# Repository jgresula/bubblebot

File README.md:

# BubbleBot

This repository contains firmware, FreeCAD and KiCad files for my [bubble blowing robot](http://make.bitovod.com/pages/bubblebot.html).

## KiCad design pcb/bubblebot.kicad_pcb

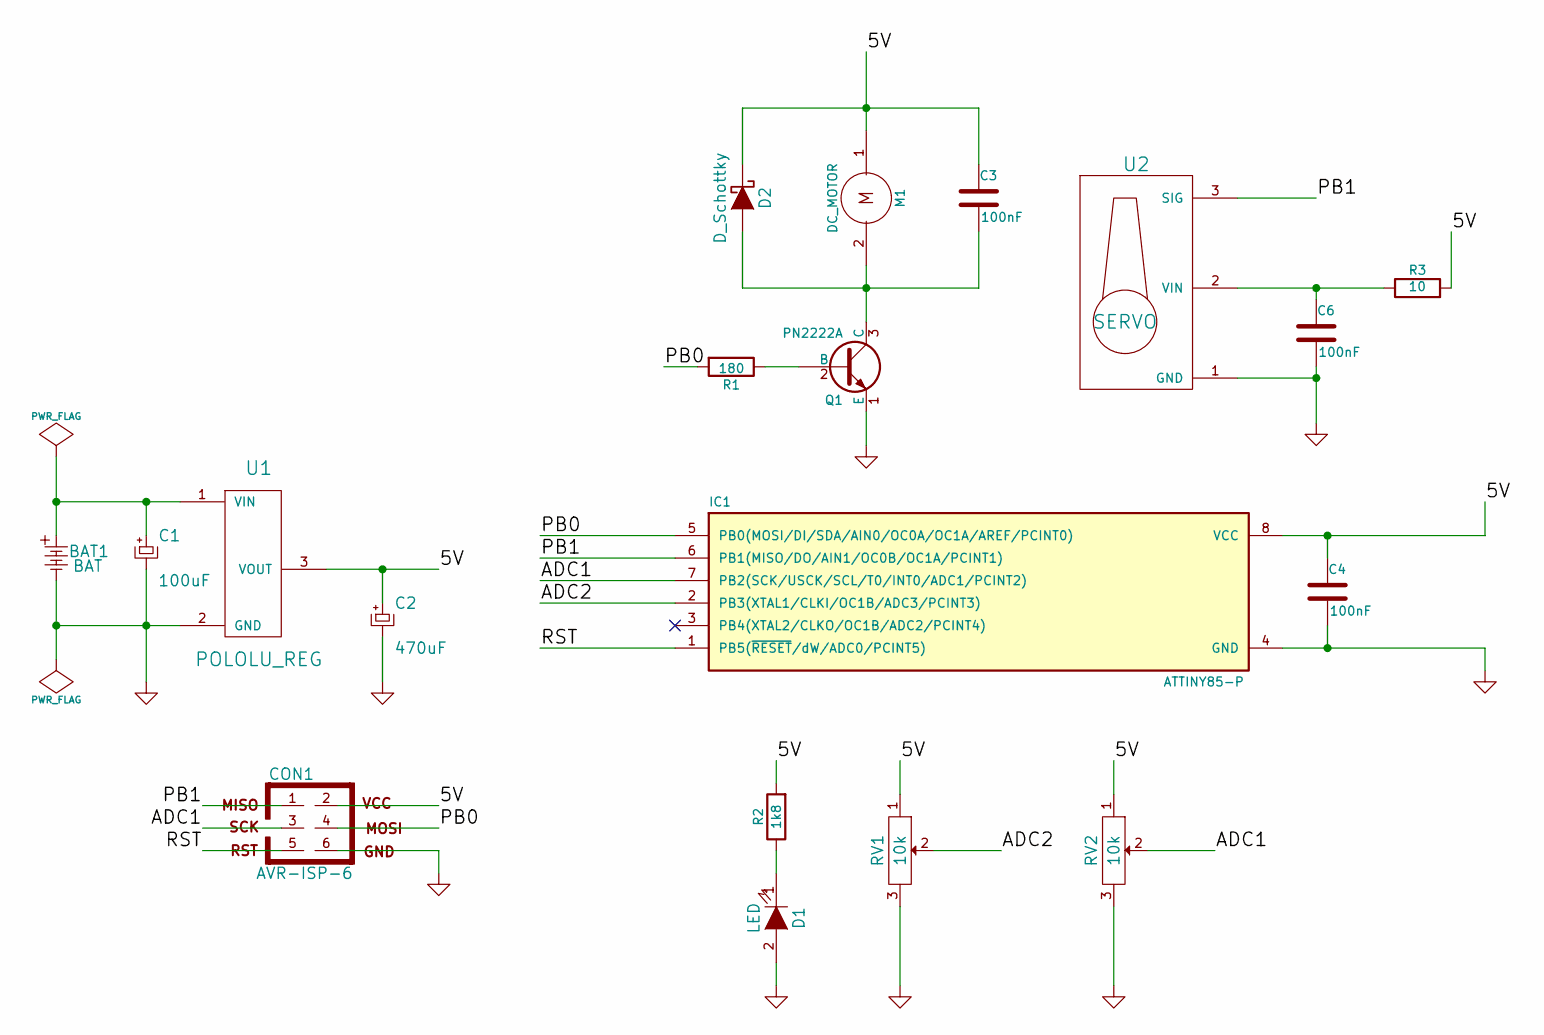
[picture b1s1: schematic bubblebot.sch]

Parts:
BAT1: BAT; Socket_Strip_Straight_1x02
C1: 100uF; C_Radial_D5_L11_P2
C2: 470uF; C_Radial_D8_L13_P3.8
C3, C4, C6: 100nF; C_Disc_D3_P2.5
CON1: AVR-ISP-6; Pin_Header_Straight_2x03
D1: LED; LED-3MM
D2: D_Schottky; Diode_DO-41_SOD81_Horizontal_RM10
IC1: ATTINY85-P; DIP-8_W7.62mm
M1: DC_MOTOR; Socket_Strip_Straight_1x02
Q1: PN2222A; TO-92_Molded_Narrow
R1: 180; Resistor_Vertical_RM5mm
R2: 1k8; Resistor_Vertical_RM5mm
R3: 10; Resistor_Vertical_RM5mm
RV1, RV2: 10k; Socket_Strip_Straight_1x03
U1: POLOLU_REG; Socket_Strip_Straight_1x03
U2: SERVO; Socket_Strip_Straight_1x03

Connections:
/5V: C2.1, C3.1, C4.1, CON1.2, D2.1 (K), IC1.8 (VCC), M1.1, R2.2, R3.2, RV1.1, RV2.1, U1.3 (VOUT)
/ADC1: CON1.3, IC1.7 (PB2(SCK/USCK/SCL/T0/INT0/ADC1/PCINT2)), RV2.2
/ADC2: IC1.2 (PB3(XTAL1/CLKI/OC1B/ADC3/PCINT3)), RV1.2
/PB0: CON1.4, IC1.5 (PB0(MOSI/DI/SDA/AIN0/OC0A/OC1A/AREF/PCI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), R1.2
/PB1: CON1.1, IC1.6 (PB1(MISO/DO/AIN1/OC0B/OC1A/PCINT1)), U2.3 (SIG)
/RST: CON1.5, IC1.1 (PB5(~RESET~/dW/ADC0/PCINT5))
GND: BAT1.2, C1.2, C2.2, C4.2, C6.2, CON1.6, D1.2 (A), IC1.4 (GND), Q1.1 (E), RV1.3, RV2.3, U1.2 (GND), U2.1 (GND)
unnamed: BAT1.1, C1.1, U1.1 (VIN)
unnamed: C3.2, D2.2 (A), M1.2, Q1.3 (C)
unnamed: C6.1, R3.1, U2.2 (VIN)
unnamed: D1.1 (K), R2.1
unnamed: Q1.2 (B), R1.1

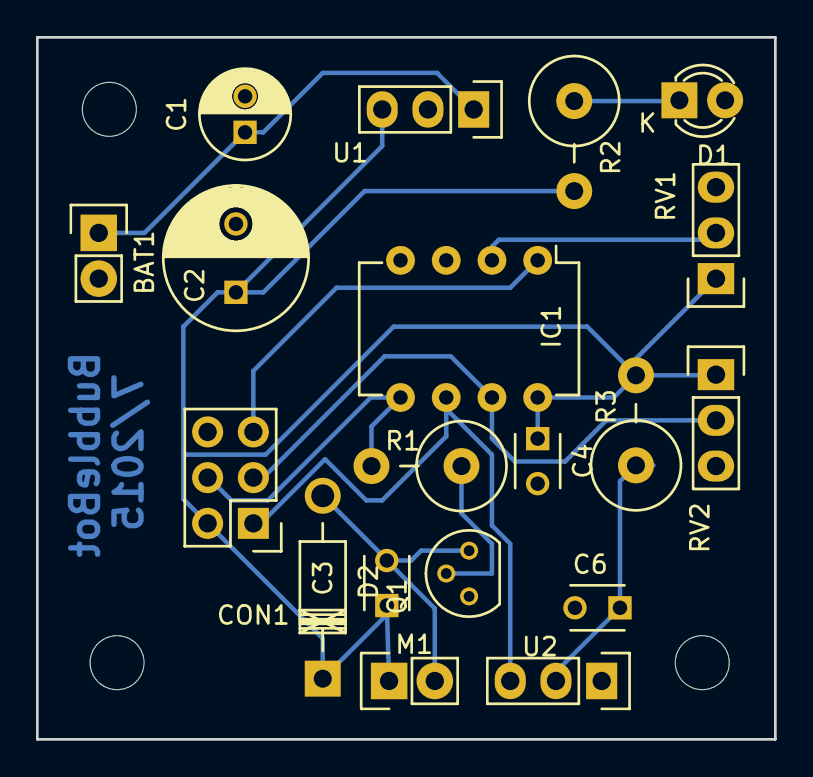
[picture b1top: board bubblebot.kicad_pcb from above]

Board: 2 copper layers, 41.0 x 39.0 mm, 19 parts (0 on the bottom side), 12 nets.

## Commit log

2015-08-18 initial import
